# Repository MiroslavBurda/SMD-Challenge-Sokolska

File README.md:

# SMD-Challenge-Sokolska
Board for learning of SMD soldering

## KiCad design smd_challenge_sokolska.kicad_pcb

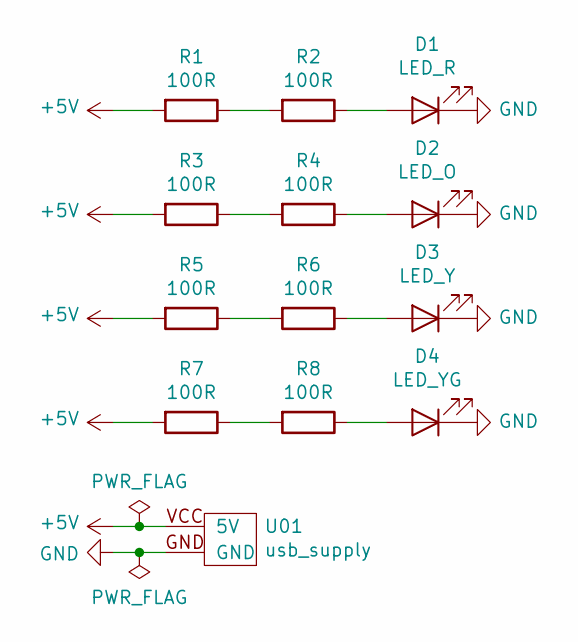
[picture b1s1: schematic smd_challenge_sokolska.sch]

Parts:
D1: LED_R; LED_1206_3216Metric_Pad1.42x1.75mm_HandSolder
D2: LED_O; LED_0805_2012Metric_Pad1.15x1.40mm_HandSolder
D3: LED_Y; LED_0603_1608Metric_Pad1.05x0.95mm_HandSolder
D4: LED_YG; LED_0402_1005Metric
R1, R2: 100R; R_1206_3216Metric_Pad1.42x1.75mm_HandSolder
R3, R4: 100R; R_0805_2012Metric_Pad1.15x1.40mm_HandSolder
R5, R6: 100R; R_0603_1608Metric_Pad1.05x0.95mm_HandSolder
R7, R8: 100R; R_0402_1005Metric
U01: usb_supply

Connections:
+5V: R1.2, R3.2, R5.2, R7.2, U01.VCC (5V)
GND: D1.1 (K), D2.1 (K), D3.1 (K), D4.1 (K), U01.GND
unnamed: D1.2 (A), R2.1
unnamed: D2.2 (A), R4.1
unnamed: D3.2 (A), R6.1
unnamed: D4.2 (A), R8.1
unnamed: R1.1, R2.2
unnamed: R3.1, R4.2
unnamed: R5.1, R6.2
unnamed: R7.1, R8.2

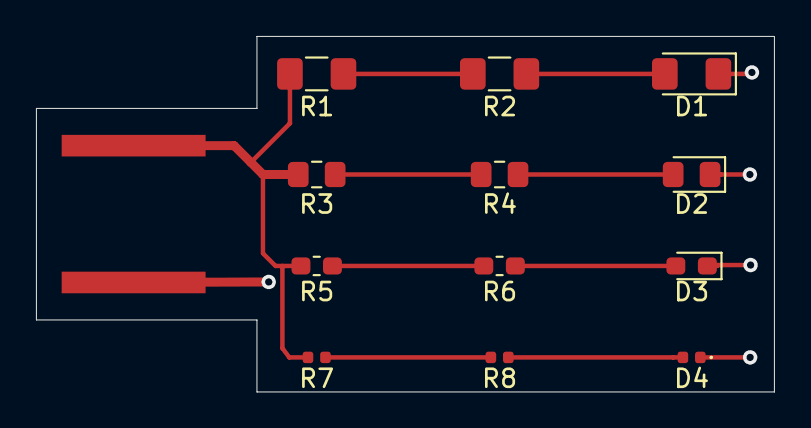
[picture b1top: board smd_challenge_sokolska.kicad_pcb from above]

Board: 2 copper layers, 41.0 x 19.8 mm, 13 parts (0 on the bottom side), 10 nets.

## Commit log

2020-11-22 first version
2020-11-22 add makefile
2020-11-22 fixed part U01
2022-09-11 hide silkscreen
